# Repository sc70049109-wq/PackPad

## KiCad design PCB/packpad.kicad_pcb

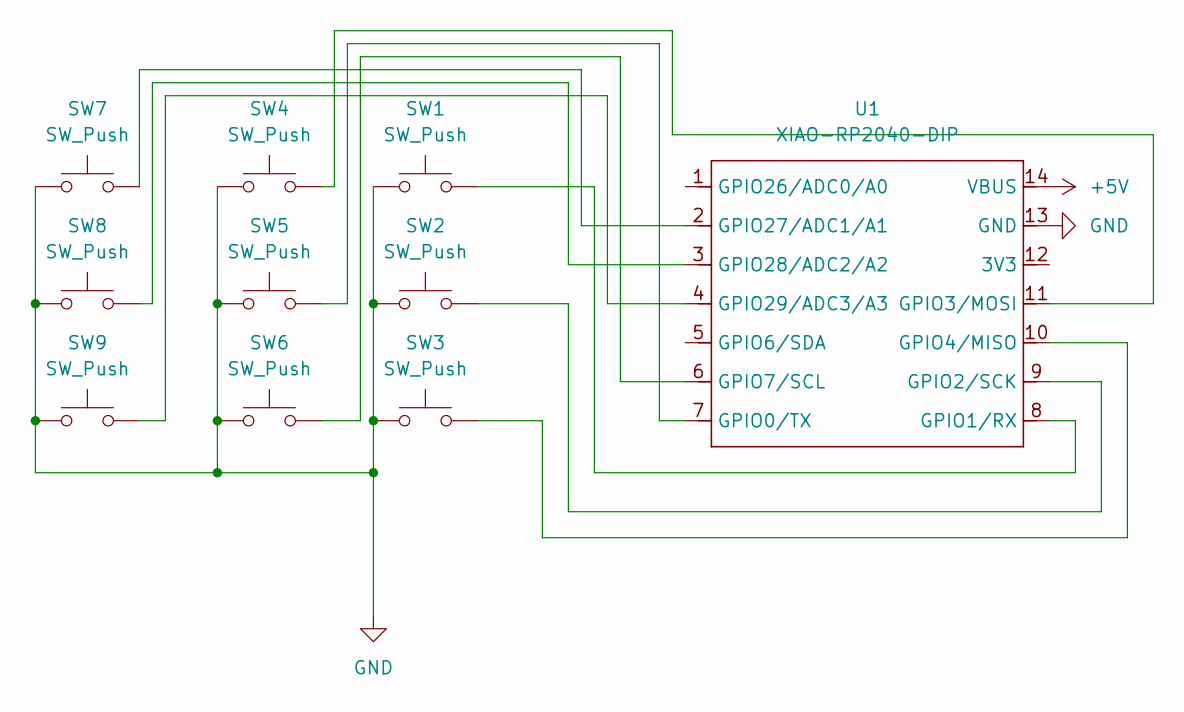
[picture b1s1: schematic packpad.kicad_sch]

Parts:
SW1, SW2, SW3, SW4, SW5, SW6, SW7, SW8, SW9: SW_Push; SW_Cherry_MX_1.00u_PCB
U1: XIAO-RP2040-DIP

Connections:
+5V: U1.14 (VBUS)
GND: SW1.1, SW2.1, SW3.1, SW4.1, SW5.1, SW6.1, SW7.1, SW8.1, SW9.1, U1.13 (GND)
unnamed: SW5.2, U1.7 (GPIO0/TX)
unnamed: SW1.2, U1.8 (GPIO1/RX)
unnamed: SW2.2, U1.9 (GPIO2/SCK)
unnamed: SW4.2, U1.11 (GPIO3/MOSI)
unnamed: SW3.2, U1.10 (GPIO4/MISO)
unnamed: SW6.2, U1.6 (GPIO7/SCL)
unnamed: SW7.2, U1.2 (GPIO27/ADC1/A1)
unnamed: SW8.2, U1.3 (GPIO28/ADC2/A2)
unnamed: SW9.2, U1.4 (GPIO29/ADC3/A3)

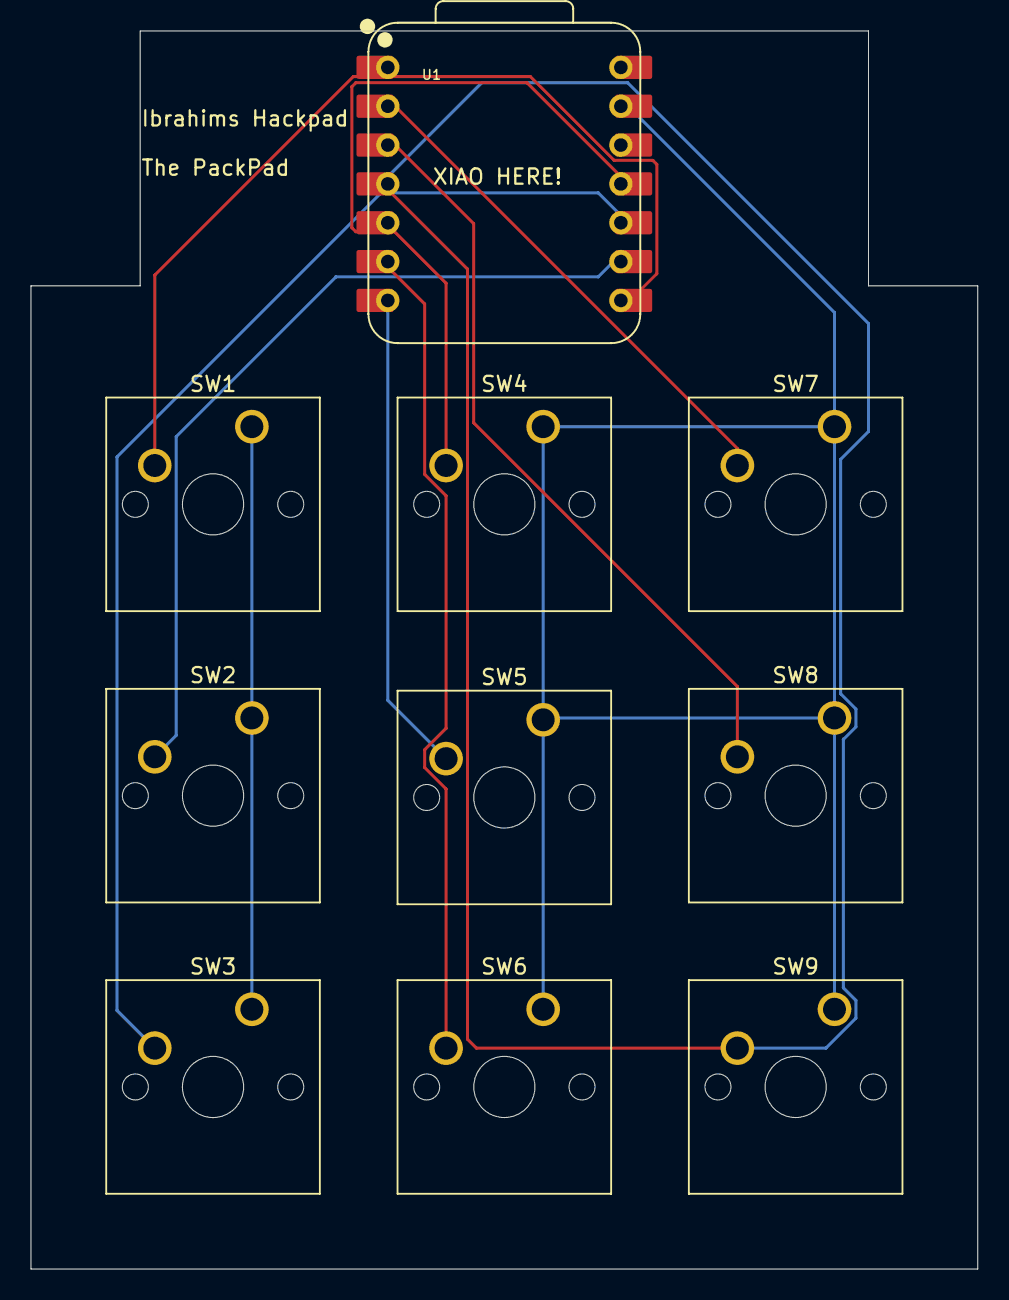
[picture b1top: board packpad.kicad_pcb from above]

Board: 2 copper layers, 61.9 x 81.0 mm, 10 parts (0 on the bottom side), 10 nets.

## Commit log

2026-01-19 Create PCB
2026-01-19 Create CAD
2026-01-19 Create iigozdn
